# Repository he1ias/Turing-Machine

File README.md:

# Turing Machine
A programmable 4-state Turing Machine with a 16-bit circular tape running on a PCB.

### How does it work?

Turing Machines are the simplest form of computer - given a state table (a small program) and an infinite tape, Turing Machines can perform any computation.

My machine has 4 states (5 if you include HALT) and a 16 bit circular tape. It can't do much - but it can run basic programs like LED blinkers, counters, and the champion 4-state Busy Beaver machine (search it up!).

The bonus of this small design is this the program is * physical *, ie. you can edit the program the computer is running by flipping the ROM switches - in real time!

You can also manually step the clock, or use the built in one and control its speed. The machine has 16 LEDs showing the tape's content, one for showing whether the computer is halted, and one showing the HIGH / LOW pulses of the clock.

### How was it made?

I started by using Seb Lague's Digital Logic Sim to get a feel for the project, as it was a tool I was comfortable using.

I then switched to Logisim, simplifying to the best of my ability the routing and system design.

I then converted my logic into the physical world, selecting parts and wiring up my schematic in KiCad.

Finally, I arranged all my components in a small 10cm x 10cm package, and then I routed my PCB using `freerouter` (thank god for autorouting!).

### How do I build it?

To build this project, I recommend JLC's PCBA. I found it cost effective to have them assemble all the SMD components for you, and then solder the rest yourself.

The `kicad-jlcpcb-tools` folder has been provided in this repository as a direct drag and drop way to order this project from JLCPCB. `BOM (All parts).csv` also details every part needed for this project.

After ordering the PCBA, you have to order the rest of the components (through hole) which are listed below.

The BOM I ended up with looks like this:

| Item | Qty | Supplier | Cost/item | Total Cost | link |
|---|---|---|---|---|---|
| JLC PCBA | 1 | JLC PCB | $65.00 | $65.00 | https://jlcpcb.com |
| OR Gate | 5 | LCSC | $0.16 | $0.80 | https://www.lcsc.com/product-detail/C41427253.html |
| Slide Switches | 10 | LCSC | $0.32 | $3.20 | https://www.lcsc.com/product-detail/C1121868.html |
| Shift Registers | 5 | 1.9 | $0.38 | $1.90 | https://www.lcsc.com/product-detail/C22449650.html |
| 3-Bit DEMUX | 1 | LCSC | $1.51 | $1.51 | https://www.lcsc.com/product-detail/C1547279.html |
| USB Power Supply | 10 | LCSC | $0.06 | $0.60 | https://www.lcsc.com/product-detail/C2345.html |
| Pentiometer | 1 | LCSC | $2.07 | $2.07 | https://www.lcsc.com/product-detail/C5824127.html |
| Estimated total shipping | 1 |  |  | $15.00 |  |

For convenience, the full KiCad-exported BOM is here, however you will need to double check prices at the time of purchase, as they are not listed here.

| Designator | Footprint | Quantity | Value | LCSC Part # |
|---|---|---|---|---|
| C1 | C_Disc_D5.0mm_W2.5mm_P2.50mm | 1 | 1nF |  |
| C2 | C_Disc_D5.0mm_W2.5mm_P2.50mm | 1 | 10nF |  |
| CDB1 | C_Disc_D5.0mm_W2.5mm_P2.50mm | 1 | 100nF |  |
| CLOCKLED1, HALTLED1, LED1, LED10, LED11, LED12, LED13, LED14, LED15, LED16, LED2, LED3, LED4, LED5, LED6, LED7, LED8, LED9 | LED0805-R-RD | 18 | XL-0805QBC | C2293 |
| CSPEED1 | RES-ADJ-TH_PDB12-M4251-104BF | 1 | Clock Speed | C5824127 |
| DISABLESYSTEMCLOCK1 | SW-SMD_MST22D18G2 | 1 | MST22D18G2 125 | C2906280 |
| LMUX1 | PDIP-16_L19.3-W6.4-P2.54-LS7.9-BL | 1 | 3-Bit DEMUX | C1547279 |
| NOT1, NOT2 | SOIC-14_L8.7-W3.9-P1.27-LS6.0-BL | 2 | 74HC04D,653 | C5590 |
| OR1 | PDIP-14_L19.3-W6.5-P2.54-LS7.6-BL | 1 | 74HC32N | C41427253 |
| PR1, PR2, PR3, PR4, PR5, PR6, PR7, RC2, RPRESET1, RPUSERCLOCK1 | R1206 | 10 | 10k | C4410 |
| RC1 | R1206 | 1 | 1k | C4410 |
| RCLOCKLED1, RHALTED1, RL1, RL10, RL11, RL12, RL13, RL14, RL15, RL16, RL2, RL3, RL4, RL5, RL6, RL7, RL8, RL9 | R1206 | 18 | R_Small_US | C4410 |
| RESET1, USERCLOCK1 | SW-SMD_4P-L5.1-W5.1-P3.70-LS6.5-TL_H1.5 | 2 | TS-1187A-B-A-B | C318884 |
| SHIFT1, SHIFT2, SHIFT3, SHIFT4, SHIFT5 | PDIP-16_L19.3-W6.4-P2.54-LS7.94-BL | 5 | 74194PC | C22449650 |
| SLA0, SLA1, SLB0, SLB1, SLC0, SLC1, SLD0, SLD1 | SW-TH_SS15E01L5 | 8 | SS15E01L5 | C1121868 |
| SMUX1 | SOT-363_L2.1-W1.3-P0.65-LS2.3-BL | 1 | 74LVC1G157GW-JSM | C49006656 |
| SWA0, SWA1, SWB0, SWB1, SWC0, SWC1, SWD0, SWD1 | SW-SMD_MST22D18G2 | 8 | Move | C2906280 |
| SYSCLOCK1 | SOIC-8_L4.9-W3.9-P1.27-LS6.0-BL | 1 | NE555DR | C7593 |
| USB1 | USB-A-TH__USB-AF-90 | 1 | JTJ-USB-AF-08 | C2345 |
| WA0, WA1, WB0, WB1, WC0, WC1, WD0, WD1 | SW-SMD_MST22D18G2 | 8 | Write | C2906280 |

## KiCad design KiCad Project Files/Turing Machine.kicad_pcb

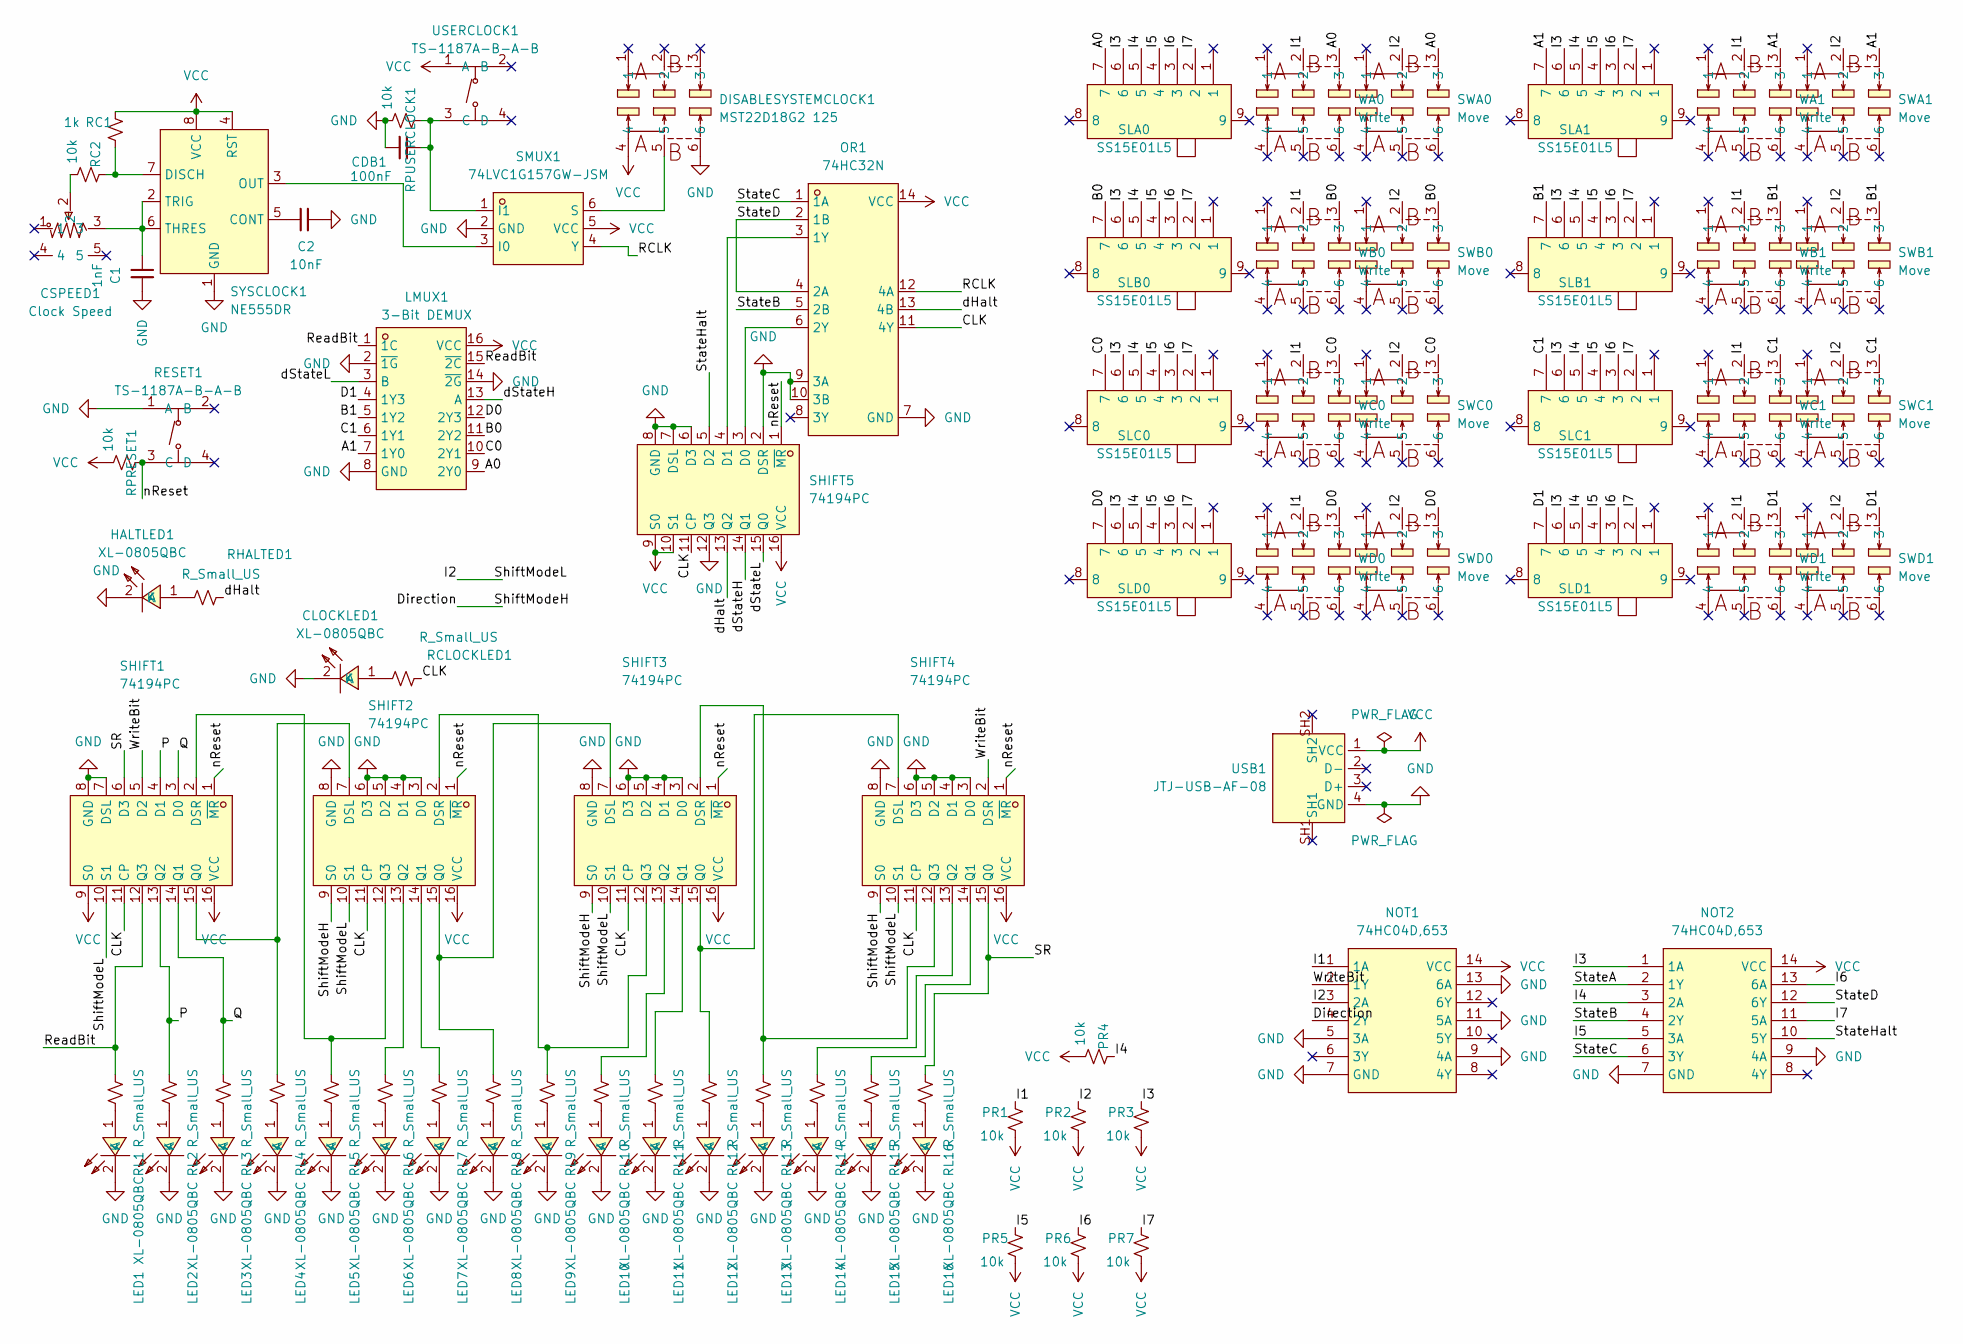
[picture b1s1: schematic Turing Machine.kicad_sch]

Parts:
C1: 1nF; C_Disc_D5.0mm_W2.5mm_P2.50mm
C2: 10nF; C_Disc_D5.0mm_W2.5mm_P2.50mm
CDB1: 100nF; C_Disc_D5.0mm_W2.5mm_P2.50mm
CLOCKLED1: XL-0805QBC; LED0805-R-RD; MPN KT-0805B; LCSC Part C2293
CSPEED1: Clock Speed; RES-ADJ-TH_PDB12-M4251-104BF; MPN PDB12-M4251-105BF; LCSC Part C5824127
DISABLESYSTEMCLOCK1: MST22D18G2 125; SW-SMD_MST22D18G2; MPN MST22D18G2 125; LCSC Part C2906280
HALTLED1: XL-0805QBC; LED0805-R-RD; MPN KT-0805B; LCSC Part C2293
LED1, LED2, LED3, LED4, LED5, LED6, LED7, LED8, LED9, LED10, LED11, LED12, LED13, LED14, LED15, LED16: XL-0805QBC; LED0805-R-RD; MPN KT-0805B; LCSC Part C2293
LMUX1: 3-Bit DEMUX; PDIP-16_L19.3-W6.4-P2.54-LS7.9-BL; MPN SN74LS156N; LCSC Part C1547279
NOT1, NOT2: 74HC04D,653; SOIC-14_L8.7-W3.9-P1.27-LS6.0-BL; MPN 74HC04D,653; LCSC Part C5590
OR1: 74HC32N; PDIP-14_L19.3-W6.5-P2.54-LS7.6-BL; MPN 74HC32N; LCSC Part C41427253
PR1, PR2, PR3, PR4, PR5, PR6, PR7: 10k; R1206
RC1: 1k; R1206
RC2: 10k; R1206
RCLOCKLED1: R_Small_US; R1206
RESET1: TS-1187A-B-A-B; SW-SMD_4P-L5.1-W5.1-P3.70-LS6.5-TL_H1.5; MPN TS-1187A-B-A-B; LCSC Part C318884
RHALTED1: R_Small_US; R1206
RL1, RL2, RL3, RL4, RL5, RL6, RL7, RL8, RL9, RL10, RL11, RL12, RL13, RL14, RL15, RL16: R_Small_US; R1206
RPRESET1: 10k; R1206
RPUSERCLOCK1: 10k; R1206
SHIFT1, SHIFT2, SHIFT3, SHIFT4, SHIFT5: 74194PC; PDIP-16_L19.3-W6.4-P2.54-LS7.94-BL; MPN SN74HC194N(LX); LCSC Part C22449650
SLA0, SLA1: SS15E01L5; SW-TH_SS15E01L5; MPN SS15E01L5; LCSC Part C1121868
SLB0, SLB1: SS15E01L5; SW-TH_SS15E01L5; MPN SS15E01L5; LCSC Part C1121868
SLC0, SLC1: SS15E01L5; SW-TH_SS15E01L5; MPN SS15E01L5; LCSC Part C1121868
SLD0, SLD1: SS15E01L5; SW-TH_SS15E01L5; MPN SS15E01L5; LCSC Part C1121868
SMUX1: 74LVC1G157GW-JSM; SOT-363_L2.1-W1.3-P0.65-LS2.3-BL; MPN 74LVC1G157GW-JSM; LCSC Part C49006656
SWA0, SWA1: Move; SW-SMD_MST22D18G2; MPN MST22D18G2 125; LCSC Part C2906280
SWB0, SWB1: Move; SW-SMD_MST22D18G2; MPN MST22D18G2 125; LCSC Part C2906280
SWC0, SWC1: Move; SW-SMD_MST22D18G2; MPN MST22D18G2 125; LCSC Part C2906280
SWD0, SWD1: Move; SW-SMD_MST22D18G2; MPN MST22D18G2 125; LCSC Part C2906280
SYSCLOCK1: NE555DR; SOIC-8_L4.9-W3.9-P1.27-LS6.0-BL; MPN NE555DR; LCSC Part C7593
USB1: JTJ-USB-AF-08; USB-A-TH__USB-AF-90; MPN 902-131A1011D10100; LCSC Part C2345
USERCLOCK1: TS-1187A-B-A-B; SW-SMD_4P-L5.1-W5.1-P3.70-LS6.5-TL_H1.5; MPN TS-1187A-B-A-B; LCSC Part C318884
WA0, WA1: Write; SW-SMD_MST22D18G2; MPN MST22D18G2 125; LCSC Part C2906280
WB0, WB1: Write; SW-SMD_MST22D18G2; MPN MST22D18G2 125; LCSC Part C2906280
WC0, WC1: Write; SW-SMD_MST22D18G2; MPN MST22D18G2 125; LCSC Part C2906280
WD0, WD1: Write; SW-SMD_MST22D18G2; MPN MST22D18G2 125; LCSC Part C2906280

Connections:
/A0: LMUX1.9 (2Y0), SLA0.7, SWA0.3, WA0.3
/A1: LMUX1.7 (1Y0), SLA1.7, SWA1.3, WA1.3
/B0: LMUX1.11 (2Y2), SLB0.7, SWB0.3, WB0.3
/B1: LMUX1.5 (1Y2), SLB1.7, SWB1.3, WB1.3
/C0: LMUX1.10 (2Y1), SLC0.7, SWC0.3, WC0.3
/C1: LMUX1.6 (1Y1), SLC1.7, SWC1.3, WC1.3
/CLK: OR1.11 (4Y), RCLOCKLED1.2, SHIFT1.11 (CP), SHIFT2.11 (CP), SHIFT3.11 (CP), SHIFT4.11 (CP), SHIFT5.11 (CP)
/D0: LMUX1.12 (2Y3), SLD0.7, SWD0.3, WD0.3
/D1: LMUX1.4 (1Y3), SLD1.7, SWD1.3, WD1.3
/Direction: NOT1.4 (2Y), SHIFT2.9 (S0), SHIFT3.9 (S0), SHIFT4.9 (S0)
/I1: NOT1.1 (1A), PR1.1, WA0.2, WA1.2, WB0.2, WB1.2, WC0.2, WC1.2, WD0.2, WD1.2
/I2: NOT1.3 (2A), PR2.1, SHIFT1.10 (S1), SHIFT2.10 (S1), SHIFT3.10 (S1), SHIFT4.10 (S1), SWA0.2, SWA1.2, SWB0.2, SWB1.2, SWC0.2, SWC1.2, SWD0.2, SWD1.2
/I3: NOT2.1 (1A), PR3.1, SLA0.6, SLA1.6, SLB0.6, SLB1.6, SLC0.6, SLC1.6, SLD0.6, SLD1.6
/I4: NOT2.3 (2A), PR4.1, SLA0.5, SLA1.5, SLB0.5, SLB1.5, SLC0.5, SLC1.5, SLD0.5, SLD1.5
/I5: NOT2.5 (3A), PR5.1, SLA0.4, SLA1.4, SLB0.4, SLB1.4, SLC0.4, SLC1.4, SLD0.4, SLD1.4
/I6: NOT2.13 (6A), PR6.1, SLA0.3, SLA1.3, SLB0.3, SLB1.3, SLC0.3, SLC1.3, SLD0.3, SLD1.3
/I7: NOT2.11 (5A), PR7.1, SLA0.2, SLA1.2, SLB0.2, SLB1.2, SLC0.2, SLC1.2, SLD0.2, SLD1.2
/P: RL2.1, SHIFT1.4 (D1), SHIFT1.13 (Q2)
/Q: RL3.1, SHIFT1.3 (D0), SHIFT1.14 (Q1)
/RCLK: OR1.12 (4A), SMUX1.4 (Y)
/ReadBit: LMUX1.1 (1C), LMUX1.15 (~2C), RL1.1, SHIFT1.12 (Q3)
/SR: RL16.1, SHIFT1.6 (D3), SHIFT4.15 (Q0)
/StateA: NOT2.2 (1Y)
/StateB: NOT2.4 (2Y), OR1.5 (2B)
/StateC: NOT2.6 (3Y), OR1.1 (1A)
/StateD: NOT2.12 (6Y), OR1.2 (1B), OR1.4 (2A)
/StateHalt: NOT2.10 (5Y), SHIFT5.5 (D2)
/WriteBit: NOT1.2 (1Y), SHIFT1.5 (D2), SHIFT4.2 (DSR)
/dHalt: OR1.13 (4B), RHALTED1.2, SHIFT5.13 (Q2)
/dStateH: LMUX1.13 (A), SHIFT5.14 (Q1)
/dStateL: LMUX1.3 (B), SHIFT5.15 (Q0)
/nReset: RESET1.3 (C), RPRESET1.1, SHIFT1.1 (~MR), SHIFT2.1 (~MR), SHIFT3.1 (~MR), SHIFT4.1 (~MR), SHIFT5.1 (~MR)
GND: C1.2, C2.2, CDB1.1, CLOCKLED1.2 (K), DISABLESYSTEMCLOCK1.6, HALTLED1.2 (K), LED1.2 (K), LED2.2 (K), LED3.2 (K), LED4.2 (K), LED5.2 (K), LED6.2 (K), LED7.2 (K), LED8.2 (K), LED9.2 (K), LED10.2 (K), LED11.2 (K), LED12.2 (K), LED13.2 (K), LED14.2 (K), LED15.2 (K), LED16.2 (K), LMUX1.2 (~1G), LMUX1.8 (GND), LMUX1.14 (~2G), NOT1.5 (3A), NOT1.7 (GND), NOT1.9 (4A), NOT1.11 (5A), NOT1.13 (6A), NOT2.7 (GND), NOT2.9 (4A), OR1.7 (GND), OR1.9 (3A), OR1.10 (3B), RESET1.1 (A), RPUSERCLOCK1.2, SHIFT1.7 (DSL), SHIFT1.8 (GND), SHIFT2.3 (D0), SHIFT2.4 (D1), SHIFT2.5 (D2), SHIFT2.6 (D3), SHIFT2.8 (GND), SHIFT3.3 (D0), SHIFT3.4 (D1), SHIFT3.5 (D2), SHIFT3.6 (D3), SHIFT3.8 (GND), SHIFT4.3 (D0), SHIFT4.4 (D1), SHIFT4.5 (D2), SHIFT4.6 (D3), SHIFT4.8 (GND), SHIFT5.2 (DSR), SHIFT5.6 (D3), SHIFT5.7 (DSL), SHIFT5.8 (GND), SHIFT5.12 (Q3), SMUX1.2 (GND), SYSCLOCK1.1 (GND), USB1.4 (GND)
unnamed: CLOCKLED1.1 (A), RCLOCKLED1.1
unnamed: CSPEED1.2, RC2.2
unnamed: HALTLED1.1 (A), RHALTED1.1
unnamed: LED1.1 (A), RL1.2
unnamed: LED2.1 (A), RL2.2
unnamed: LED3.1 (A), RL3.2
unnamed: LED4.1 (A), RL4.2
unnamed: LED5.1 (A), RL5.2
unnamed: LED6.1 (A), RL6.2
unnamed: LED7.1 (A), RL7.2
unnamed: LED8.1 (A), RL8.2
unnamed: LED9.1 (A), RL9.2
unnamed: LED10.1 (A), RL10.2
unnamed: LED11.1 (A), RL11.2
unnamed: LED12.1 (A), RL12.2
unnamed: LED13.1 (A), RL13.2
unnamed: LED14.1 (A), RL14.2
unnamed: LED15.1 (A), RL15.2
unnamed: LED16.1 (A), RL16.2
unnamed: OR1.3 (1Y), SHIFT5.4 (D1)
unnamed: OR1.6 (2Y), SHIFT5.3 (D0)
unnamed: RL5.1, SHIFT1.2 (DSR), SHIFT2.12 (Q3)
unnamed: RL4.1, SHIFT1.15 (Q0), SHIFT2.7 (DSL)
unnamed: RL9.1, SHIFT2.2 (DSR), SHIFT3.12 (Q3)
unnamed: RL8.1, SHIFT2.15 (Q0), SHIFT3.7 (DSL)
unnamed: RL7.1, SHIFT2.14 (Q1)
unnamed: RL6.1, SHIFT2.13 (Q2)
unnamed: RL13.1, SHIFT3.2 (DSR), SHIFT4.12 (Q3)
unnamed: RL12.1, SHIFT3.15 (Q0), SHIFT4.7 (DSL)
unnamed: RL11.1, SHIFT3.14 (Q1)
unnamed: RL10.1, SHIFT3.13 (Q2)
unnamed: RL15.1, SHIFT4.14 (Q1)
unnamed: RL14.1, SHIFT4.13 (Q2)
unnamed: SMUX1.3 (I0), SYSCLOCK1.3 (OUT)
unnamed: CDB1.2, RPUSERCLOCK1.1, SMUX1.1 (I1), USERCLOCK1.3 (C)
unnamed: DISABLESYSTEMCLOCK1.5, SMUX1.6 (S)
unnamed: C2.1, SYSCLOCK1.5 (CONT)
unnamed: RC1.1, RC2.1, SYSCLOCK1.7 (DISCH)
unnamed: C1.1, CSPEED1.3, SYSCLOCK1.2 (TRIG), SYSCLOCK1.6 (THRES)
VCC: DISABLESYSTEMCLOCK1.4, LMUX1.16 (VCC), NOT1.14 (VCC), NOT2.14 (VCC), OR1.14 (VCC), PR1.2, PR2.2, PR3.2, PR4.2, PR5.2, PR6.2, PR7.2, RC1.2, RPRESET1.2, SHIFT1.9 (S0), SHIFT1.16 (VCC), SHIFT2.16 (VCC), SHIFT3.16 (VCC), SHIFT4.16 (VCC), SHIFT5.9 (S0), SHIFT5.10 (S1), SHIFT5.16 (VCC), SMUX1.5 (VCC), SYSCLOCK1.4 (RST), SYSCLOCK1.8 (VCC), USB1.1 (VCC), USERCLOCK1.1 (A)

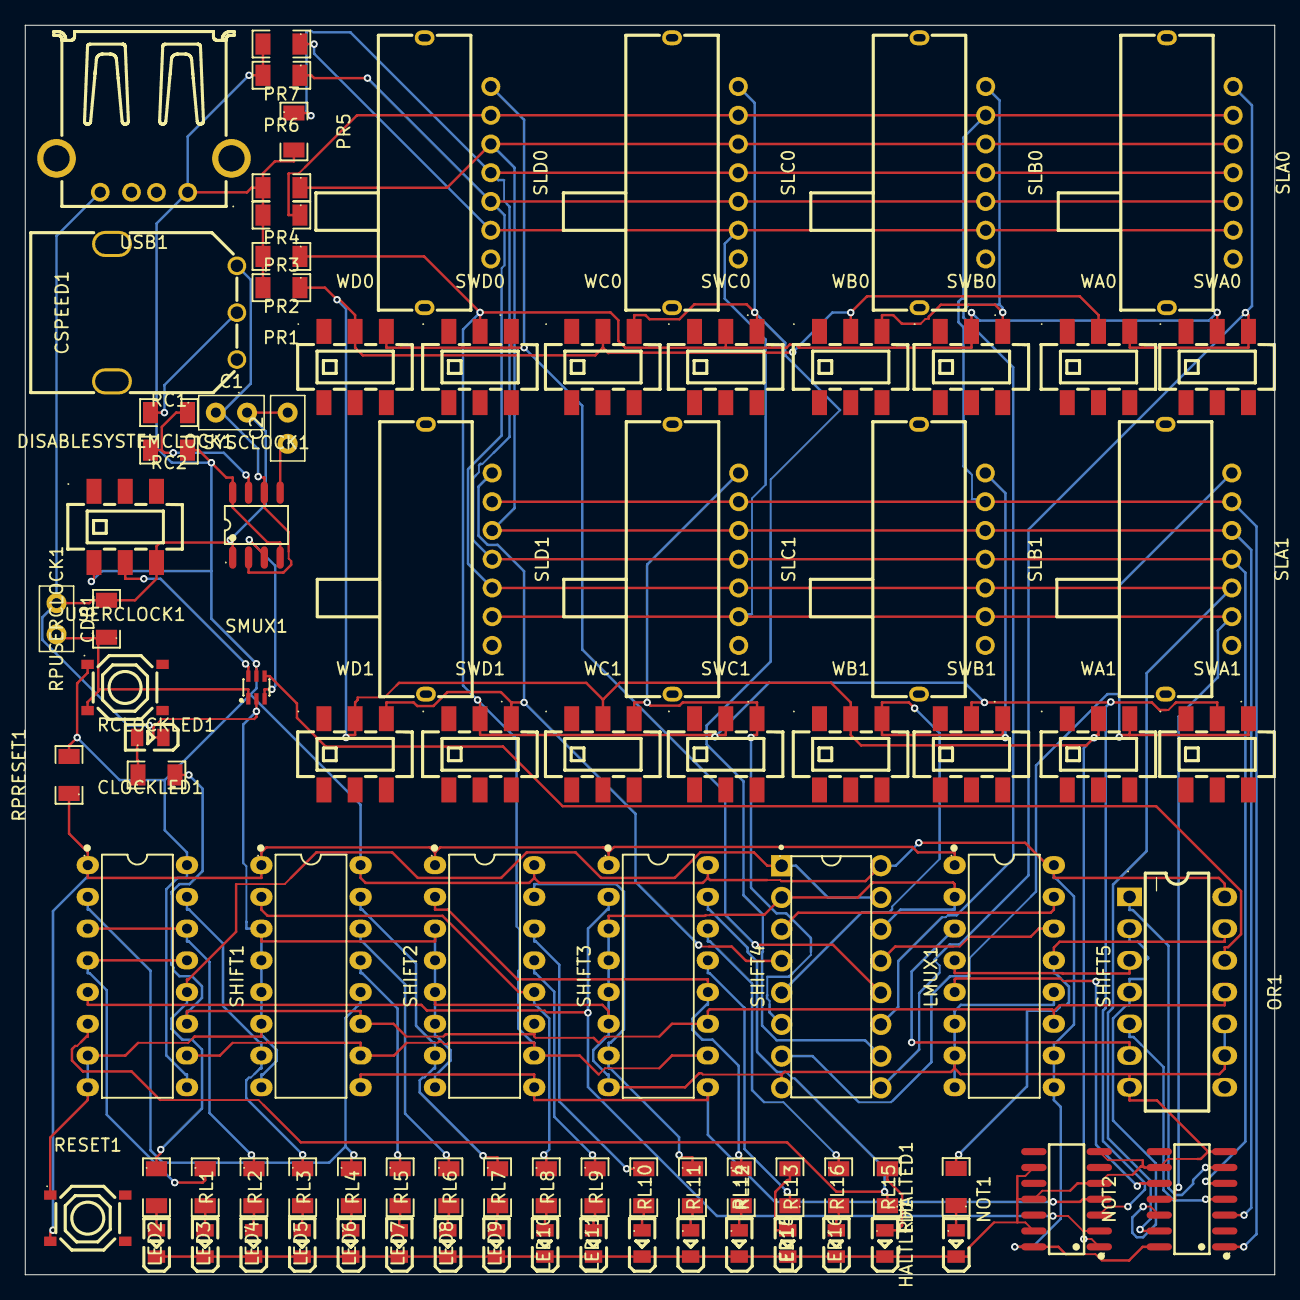
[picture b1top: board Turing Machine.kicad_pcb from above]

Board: 2 copper layers, 100.0 x 100.0 mm, 90 parts (0 on the bottom side), 72 nets.
